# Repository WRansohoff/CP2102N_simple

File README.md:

# CP2102N USB \<-\> UART Board

This is a simple reference implementation of a board using the `CP2102N` USB / Serial bridge. It has a micro-USB connector on one side, and TX / RX / 3.3V / Ground pins on the other.

The other USART signals provided by the `CP2102N` are also broken out on two rows of headers along the side of the board. I haven't tested them because I don't usually use those signals, but it seemed like a good idea to make them available.

# Current Status

This is the second revision of a design that I've had some success with. I've only tested the TX / RX signals, but those seem to work fine.

I'm still waiting to receive boards with this actual design, though, so you should still think of this board as untested for now.

# Schematic and Board Renders

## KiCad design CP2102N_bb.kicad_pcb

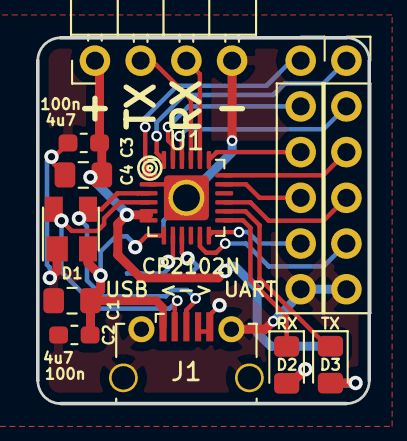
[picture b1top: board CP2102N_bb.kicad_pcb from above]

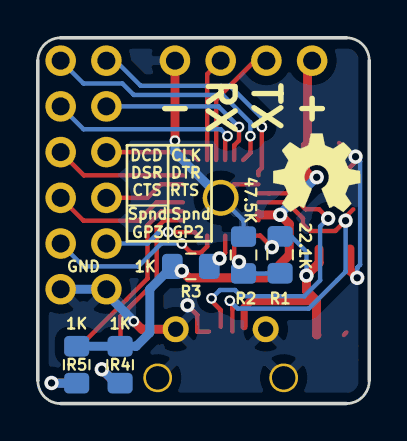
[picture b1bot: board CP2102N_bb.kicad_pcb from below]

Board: 2 copper layers, 18.4 x 20.3 mm, 17 parts (5 on the bottom side), 23 nets.

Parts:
C1, C4: 4u7; C_0805_2012Metric_Pad1.15x1.40mm_HandSolder
C2, C3: 100n; C_0603_1608Metric_Pad1.05x0.95mm_HandSolder
D1: SP0503BAHT; SOT-143
D2: RX; LED_0805_2012Metric_Pad1.15x1.40mm_HandSolder
D3: TX; LED_0805_2012Metric_Pad1.15x1.40mm_HandSolder
J1: USB_B_Micro; MyMicroUSB
J2: UART; PinHeader_1x04_P2.54mm_Horizontal
J3, J4: Other; PinSocket_1x06_P2.54mm_Vertical
R1: 22.1K; R_0805_2012Metric_Pad1.15x1.40mm_HandSolder
R2: 47.5K; R_0805_2012Metric_Pad1.15x1.40mm_HandSolder
R3, R4, R5: 1K; R_0805_2012Metric_Pad1.15x1.40mm_HandSolder
U1: CP2102N; QFN-24-1EP_4x4mm_HandSolder

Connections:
CLK: J3.1, U1.1
CTS: J4.3, U1.18
DCD: J4.1, U1.24
DSR: J4.2, U1.22
DTR: J3.2, U1.23
GND: C1.2, C2.2, C3.2, C4.1, D1.1, J1.4, J1.5, J1.6, J2.4, J3.6, J4.6, R2.1, U1.2, U1.25
GPIO2: J3.5, U1.12
GPIO3: J4.5, U1.11
unnamed: D2.1, U1.13
unnamed: D2.2, R4.2
unnamed: D3.1, U1.14
unnamed: D3.2, R5.1
unnamed: R1.1, R2.2, U1.8
unnamed: R3.1, U1.9
RTS: J3.3, U1.19
RX: J2.3, U1.20
Suspend: J3.4, U1.17
TX: J2.2, U1.21
USB_DM: D1.4, J1.2, U1.4
USB_DP: D1.3, J1.3, U1.3
VAA: C3.1, C4.2, J2.1, R3.2, R4.1, R5.2, U1.5, U1.6
VBUS: C1.1, C2.1, D1.2, J1.1, R1.2, U1.7
~Suspend: J4.4, U1.15

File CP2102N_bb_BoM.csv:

Part ID,Part type,Part size (Imperial),Part value,Example Digikey Item(s),Cost (qty: x),Comment
"C1, C4",Capacitor,0805,4.7 μF,https://www.digikey.com/short/pdb9mj,$0.26,
"C2, C3",Capacitor,0603,100 nF,https://www.digikey.com/short/pdb948,$0.20,
D1,TVS Diode Network,SOT-143-4,SP0503,https://www.digikey.com/short/pdhfqd,$0.82,3-in-1 TVS diodes for USB data line filtering. These diodes should protect the two differential data lines and the positive power line.
"D2, D3",LED,0805,Any Colors,"https://www.digikey.com/short/pdb9m9
https://www.digikey.com/short/pdb9hq",$0.34,"""Transmit"" and ""receive"" LEDs - use whatever colors you prefer. D2 is ""receive"", D3 is ""transmit"". It's probably a good idea to use different colors."
J1,USB Connector,Micro-B Socket,N/A,https://www.digikey.com/short/pdhw81,$2.07,"Micro-USB connector for battery charging and USB communication. I'm still working through a reel of cheap-o micro-B sockets that I ordered awhile ago, but they seem to fit the ""Wuerth_629105150521"" footprint in KiCAD."
J2,Pin Header,"0.1""",1x4,https://www.digikey.com/short/pdhw3q,$0.13,"Main UART header: ""+3.3V"", ""RX"", ""TX"", and ""Ground""."
"J3, J4",Pin Header,"0.1""",1x6,https://www.digikey.com/short/pdb983,$0.32,Headers for other USART signals.
R1,Resistor,0805,22.1 KΩ (1%),https://www.digikey.com/short/pdb9zz,$0.10,One of two resistors used in a voltage divider required by the internal voltage regulator.
R2,Resistor,0805,47.5 KΩ (1%),https://www.digikey.com/short/pdb9zh,$0.10,One of two resistors used in a voltage divider required by the internal voltage regulator.
"R3, R4, R5",Resistor,0805,1 KΩ,https://www.digikey.com/short/pdb9p1,$0.20,"R3 is the reset pin's pull-up resistor. R4 and R5 are current-limiting resistors for the ""transmit"" and ""receive"" LEDs."
U1,USB / Serial Bridge,QFN-24 (4x4mm),CP2102N-A01,https://www.digikey.com/short/pdb9qt,$1.35,The main USB / UART bridge chip.
Total:,,,,,$5.89,

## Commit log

2019-10-26 Add first draft of a Readme.
2019-10-26 Add 'library table' file (?)
2019-10-26 Add Bill of Materials.
2019-10-26 Add schematic file.
2019-10-26 Add project file.
2019-10-26 Add PCB file.
2019-10-26 Add custom footprints.
2019-10-26 Add initial renders of the board.
2019-10-26 Add renders to the Readme.
2019-10-26 Update project to use a local version of the hand-solderable QFP-24 footprint.
